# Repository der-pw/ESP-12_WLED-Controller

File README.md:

# ESP-12_WLED-Controller V1.3 

[English Version below](https://github.com/der-pw/ESP-12_WLED-Controller#english)

---

Designidee eines EPS-12(E/F) basierten NeoPixel (WS2812B, WS2811, SK6812)-Controller speziell für [WLED](https://github.com/Aircoookie/WLED) oder auch Alternativen.

### tl;dr
Ich habe einige Tests zur Stromaufnahme am ESP-32_WLED-Controller durchgeführt. Da beide Controller im Bereich des MOSFET gleich aufgebaut sind, lassen sich die Erkenntnisse übertragen.  
Let's talk about [maximum ratings](https://github.com/der-pw/ESP-32_WLED-Controller/blob/main/maximum_ratings.md)

### Übersicht:
 - [Versionen](https://github.com/der-pw/ESP-12_WLED-Controller#versionen)
 - [Gehäuse](https://github.com/der-pw/ESP-12_WLED-Controller#gehäuse) 
 - [Einstellungen](https://github.com/der-pw/ESP-12_WLED-Controller#einstellungen)
 - [Teileliste](https://github.com/der-pw/ESP-12_WLED-Controller#teileliste)
 - [Anschluss Hinweise](wiring.md) ->

Die Idee war es, einen Controller zu bauen, der mit Pegelwandler arbeitet um das Datensignal, welches der ESP8266 nur mit 3,3V Pegel ausgibt, auf die vom LED-Strip benötigten 5V zu setzen. Gerade bei langen Datenleitungen kann ein 3,3V-Pegel sich schneller "verwaschen". 
Als Levelshifter werwende ich einen **74LVC1G125**.
Zusätzlich kann die Versorgungsspannung für den LED-Strip über einen P-Kanal MOSFET abgeschaltet werden. Auch im ausgeschalteten Zustand verbrauchen die NEOPIXEL-Strips Strom (ca. 1mA/Pixel).   
Praktischerweise bietet WLED hier seit einiger Zeit, die Möglichkeit über einen frei definierten Pin ein "Relay" zu schalten.
Vor dem P-MOSFET sitzt ein weiterer N-MOSFET. Einmal funktioniert dieser als Treiber um den P-MOSFET mit 5V Logikpegel zu schalten und zum anderen als Inverter, damit der Haupt-MOSFET praktisch "active HIGH" am GPIO12 des ESP2866 durchschaltet.

### Versionen:
 - 0.9 erstes Layout veröffentlicht
 - 1.0 kleine Änderungen und Fehler beseitigt
 - - 1.01 C1 und C2 Korrektur der Werte (statt 10nF 10µF) hat keine Auswirkung auf die Platine
 - - 1.1 Gatewiderstand R9 hinzugefügt
 - - 1.2 Gatewiderstand Wert auf 300Ohm geändert
 - - 1.3 Platinenlayout überarbeitet  
 THT-MOSFET entfernt und dafür ...    
 Leiterbahn verbreitert und auf zwei Lagen verteilt  
 zweiter C2 Kondensator  
 Lötjumper unter R6 zum Überbrücken gesetzt  
 zweiter GND Anschluss am Terminal  
 Datenpin von IO4 auf IO2 gelegt [Fehler im Design](https://github.com/der-pw/ESP-12_WLED-Controller/issues/2#issuecomment-1024920433).

### Gehäuse

Es gibt ein simples Gehäuse. 
Die beiden Geäusehälften werden zusammen geklipst.
Die Platine wird mittels 2x5mm Linsenkopfschrauben (Grobgewinde) im Gehäuse befestigt.

### Einstellungen
Die Platine verwendet folgendes Pin-Setting.  
Auf **GPIO0** kann ein externer Button verwendet werden, zum Ein- und Ausschalten und zusätzlich initiert man darüber den Flashvorgang.  
An **GPIO2** hängt das Datensignal und über **GPIO12** wird der MOSFET geschaltet.

### Teileliste

| Refs | Qty | Component | Description |
| ----- | --- | ---- | ----------- |
| C1 | 1 | 10µF | 0805 10µF |
| C2 | 1 | 47F | 0805 47µF oder 22µF |
| aC2 | 1 | 100µF | alternativer Footprint in 1206 für größere Kerkos |
| C3, C5 | 2 | 100nF | 0805 100nF |
| C4 | 1 | 1000µF | Elko radial 1000µF 6.3V RM3.5 d=8mm l=11.5mm |
| D1 | 1 | Freilaufdiode | SS14 DO-214 |
| J1 | 1 | Screw_Terminal_01x05 |  |
| J2 | 1 | Conn_01x04_Male | Buchsenleiste RM2.54mm |
| JP1 | 1 | BTN/FLASH | Jumper mit Pinheader RM2.54 |
| JP2 | 1 | Jumper_2_Open | Lötbrücke auf der Rückseite für R6 |
| Q1 | 1 | IRLML6344 | MOSFET N-Kanal 30 V 5A SOT-23 |
| Q2 | 1 | IRF7410 | MOSFET P-Kanal -12 V -16A SO-8 |
| R1, R2, R3, R4, R5, R7, R8 | 7 | 10k | 0805 10kΩ |
| R6 | 1 | 470R | 0805 470Ω |
| R9 | 1 | 300R | 0805 300Ω |
| SW1 | 1 | SW_RST | 6mm x3.5mm Push Button SMD|
| U1 | 1 | TS1117-3.3 | Linearregler 3.3V fix alt. AMS1117-3.3, SOT-223 |
| U2 | 1 | ESP-12F | ESP-12F (ESP8266) Wifi-Modul |
| U4 | 1 | 74LVC1G125 | Single Buffer Gate Tri-State als Logic Level Converter, SOT-23-5 |

Diese Platine kann mit einem [fertigen Binary](https://install.wled.me/) verwendet werden.

## Dankeschön!  

Ein besonderer Dank geht an [Aircoookie](https://github.com/Aircoookie) und allen Beteiligten, die am [WLED](https://github.com/Aircoookie/WLED) Projekt mitarbeiten.

----
## English

### tl;dr
I did some power consumption tests on the ESP-32_WLED controller. Both controllers have the same structure in the MOSFET area, the results can be transferred.  
Let's talk about [maximum ratings](https://github.com/der-pw/ESP-32_WLED-Controller/blob/main/maximum_ratings.md)

----

Design idea of an EPS-12 (E / F) based NeoPixel (WS2812B, WS2811, SK6812) controller especially for WLED or alternatives.

Overview:
 - [Versions](https://github.com/der-pw/ESP-12_WLED-Controller#versions)
 - [Case](https://github.com/der-pw/ESP-12_WLED-Controller#case) 
 - [Settings](https://github.com/der-pw/ESP-12_WLED-Controller#settings)
 - [Parts list](https://github.com/der-pw/ESP-12_WLED-Controller#parts-list)
 - [Connecting Hints](wiring.md) ->

The idea was to build a controller that works with level converters to set the data signal, which the ESP8266 only outputs with a 3.3V level, to the 5V required by the LED strip. Especially with long data lines, a 3.3V level can "fading" more quickly.
As the level shifter I use a **74LVC1G125**.
In addition, the supply voltage for the LED strip can be switched off via a P-Channel MOSFET. Even when switched off, the NEOPIXEL strips consume electricity (approx. 1mA/pixel).
Conveniently, WLED offers the option of switching a "relay" via a freely defined pin. https://github.com/Aircoookie/WLED/issues/631#issuecomment-578551872
Another N-MOSFET sits in front of the P-MOSFET. On the one hand, this works as a driver to operate the P-MOSFET with a 5V logic level and on the other hand as an inverter, so that the main MOSFET switches through practically "active HIGH" on the GPIO12 of the ESP2866.

### Versions:
 - 0.9 first layout published
 - 1.0 minor changes and bugs fixed
 - - 1.01 C1 and C2 wrong Values fixed (10µF instead of 10nF) has no effects of the PCB
 - - 1.1 added gate resistor R9
 - - 1.2 change gate resisitr value to 300Ohm
 - - 1.3 board layout revised  
 THT MOSFET removed and for that...  
 Traces widened and divided onto two layers  
 second alternative C2 capacitor  
 Solder jumper placed under R6 for bridging  
 second GND connector on the terminal.  
 Data pin placed from IO4 to IO2 [Error in design](https://github.com/der-pw/ESP-12_WLED-Controller/issues/2#issuecomment-1024920433). 

### Case

There is a simple case. The two halves of the housing are clipped together. The circuit board is attached to the housing by means of 2x5mm pan head screws (coarse thread).

### Settings
The board uses the following pin setting.
An external button can be used on GPIO0 to switch it on and off and also to initiate the flash process.
The data signal is connected to GPIO2 and the MOSFET is switched via GPIO12.

### Parts list

| Refs | qty | components | Description |
| ----- | --- | ---- | ----------- |
| C1 | 1 | 10µF | 0805 10µF |
| C2 | 1 | 47F | 0805 47µF or 22µF |
| aC2 | 1 | 100µF | alternative footprint in 1206 for larger caps |
| C3, C5 | 2 | 100nF | 0805 100nF |
| C4 | 1 | 1000µF | Capacitor radial 1000µF 6.3V pich3.5 d=8mm l=11.5mm |
| D1 | 1 | Flyback diode | SS14 DO-214 |
| J1 | 1 | Screw_Terminal_01x05 | |
| J2 | 1 | Conn_01x04_Male | Socket strip pitch 2.54mm |
| JP1 | 1 | BTN/FLASH | Jumper with pin header pitch 2.54 |
| JP2 | 1 | Jumper_2_Open | Solder bridge on the back for R6 |
| Q1 | 1 | IRLML6344 | MOSFET N-channel 30V 5A SOT-23 |
| Q2 | 1 | IRF7410 | MOSFET P-channel -12V -16A SO-8 |
| R1, R2, R3, R4, R5, R7, R8 | 7 | 10k | 0805 10kΩ |
| R6 | 1 | 470R | 0805 470Ω |
| R9 | 1 | 300R | 0805 300Ω |
| SW1 | 1 | SW_RST | 6mm x3.5mm Push Button SMD|
| U1 | 1 | TS1117-3.3 | Linear regulator 3.3V fix old. AMS1117-3.3, SOT-223 |
| U2 | 1 | ESP-12F | ESP-12F (ESP8266) Wifi Module |
| U4 | 1 | 74LVC1G125 | Single Buffer Gate Tri-State as Logic Level Converter, SOT-23-5 |

PCB can be used with a [pre compiled binary](https://install.wled.me/).

## Thanks!  

Special thanks to [Aircoookie](https://github.com/Aircoookie) and all the contributors at the [WLED](https://github.com/Aircoookie/WLED) project.

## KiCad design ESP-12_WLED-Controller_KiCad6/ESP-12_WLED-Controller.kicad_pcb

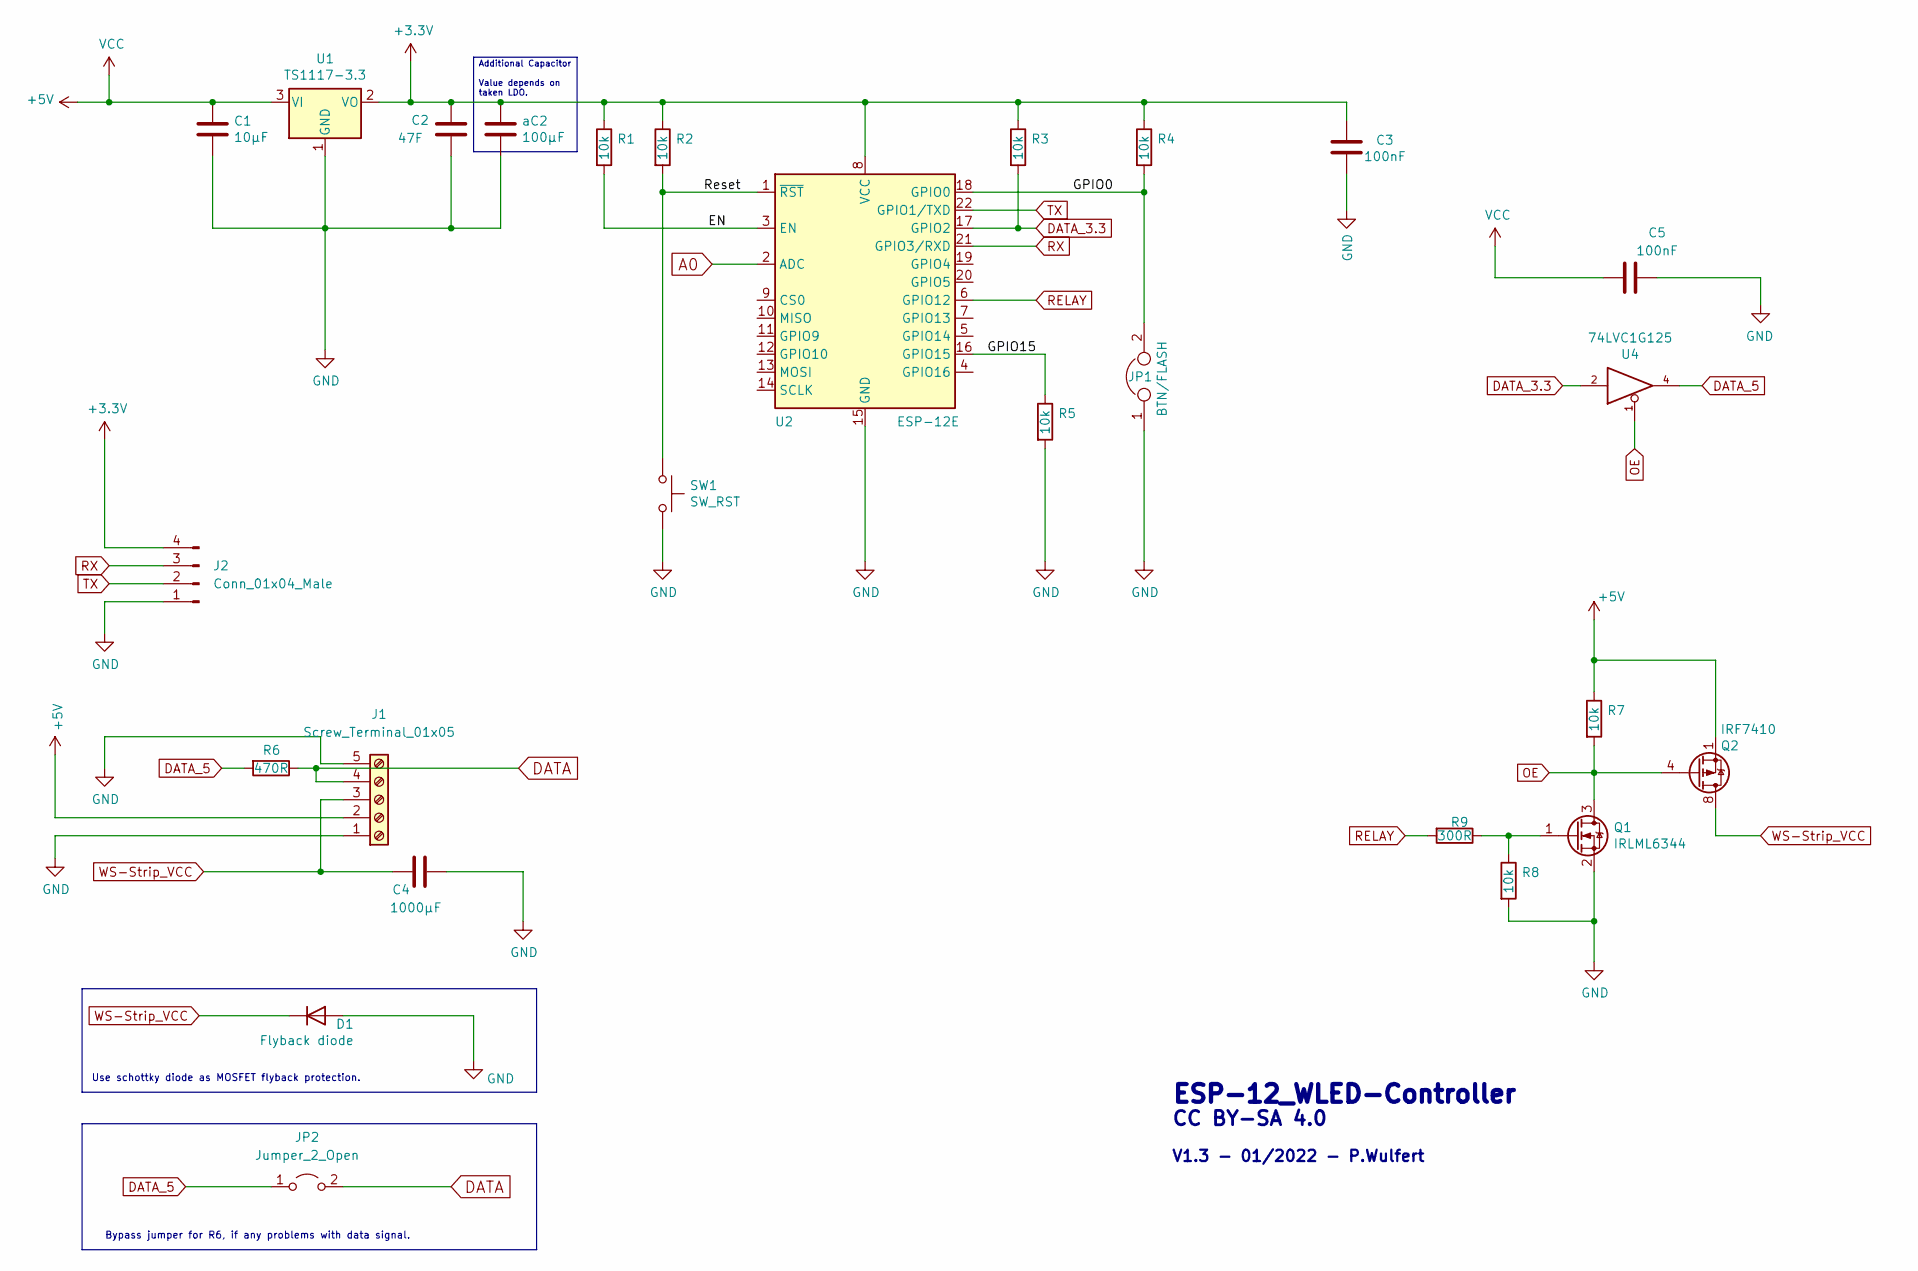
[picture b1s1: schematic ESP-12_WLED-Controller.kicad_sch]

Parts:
C1: 10µF; C_0805_2012Metric_Pad1.18x1.45mm_HandSolder; LCSC C1713
C2: 47F; C_0805_2012Metric_Pad1.18x1.45mm_HandSolder; LCSC C1713
C3, C5: 100nF; C_0805_2012Metric_Pad1.18x1.45mm_HandSolder; LCSC C49678
C4: 1000µF; CP_Radial_D8.0mm_P3.50mm; LCSC C189254
D1: Flyback diode; D_SMA_Handsoldering; LCSC C2480
J1: Screw_Terminal_01x05; TerminalBlock_bornier-5_P5.08mm
J2: Conn_01x04_Male; PinSocket_1x04_P2.54mm_Vertical
JP1: BTN/FLASH; PinHeader_1x02_P2.54mm_Vertical; LCSC C390678
JP2: Jumper_2_Open; SolderJumper-2_P1.3mm_Open_RoundedPad1.0x1.5mm
Q1: IRLML6344; SOT-23; LCSC C693370
Q2: IRF7410; SOIC-8_3.9x4.9mm_P1.27mm; LCSC C152423
R1, R2, R3, R4, R5, R7, R8: 10k; R_0805_2012Metric_Pad1.20x1.40mm_HandSolder; LCSC C17617
R6: 470R; R_0805_2012Metric_Pad1.20x1.40mm_HandSolder; LCSC C114564
R9: 300R; R_0805_2012Metric_Pad1.20x1.40mm_HandSolder; LCSC C17617
SW1: SW_RST; SW_SPST_CK_RS282G05A3
U1: TS1117-3.3; SOT-223-3_TabPin2; LCSC C410833
U2: ESP-12E; LCSC C82891
U4: 74LVC1G125; SOT-23-5; LCSC C12518
aC2: 100µF; C_1206_3216Metric_Pad1.33x1.80mm_HandSolder

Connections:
+3V3: C2.1, C3.2, J2.4, R1.1, R2.1, R3.1, R4.1, U1.2 (VO), U2.8 (VCC), aC2.1
+5V: C1.1, C5.2, J1.2, Q2.1 (S), Q2.2 (S), Q2.3 (S), R7.1, U1.3 (VI), U4.5 (VCC)
/EN: R1.2, U2.3 (EN)
/GPIO0: JP1.2, R4.2, U2.18 (GPIO0)
/GPIO15: R5.1, U2.16 (GPIO15)
/Reset: R2.2, SW1.1, U2.1 (~RST)
A0: U2.2 (ADC)
DATA: J1.4, JP2.2 (B), R6.1
DATA_3.3: R3.2, U2.17 (GPIO2), U4.2
DATA_5: JP2.1 (A), R6.2, U4.4
GND: C1.2, C2.2, C3.1, C4.2, C5.1, D1.2 (A), J1.1, J1.5, J2.1, JP1.1, Q1.2 (S), R5.2, R8.2, SW1.2, U1.1 (GND), U2.15 (GND), U4.3 (GND), aC2.2
unnamed: Q1.1 (G), R8.1, R9.1
OE: Q1.3 (D), Q2.4 (G), R7.2, U4.1
RELAY: R9.2, U2.6 (GPIO12)
RX: J2.3, U2.21 (GPIO3/RXD)
TX: J2.2, U2.22 (GPIO1/TXD)
WS-Strip_VCC: C4.1, D1.1 (K), J1.3, Q2.5 (D), Q2.6 (D), Q2.7 (D), Q2.8 (D)

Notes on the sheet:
ESP-12_WLED-Controller
Bypass jumper for R6, if any problems with data signal.
Additional Capacitor Value depends on taken LDO.
V1.3 - 01/2022 - P.Wulfert
CC BY-SA 4.0
Use schottky diode as MOSFET flyback protection.

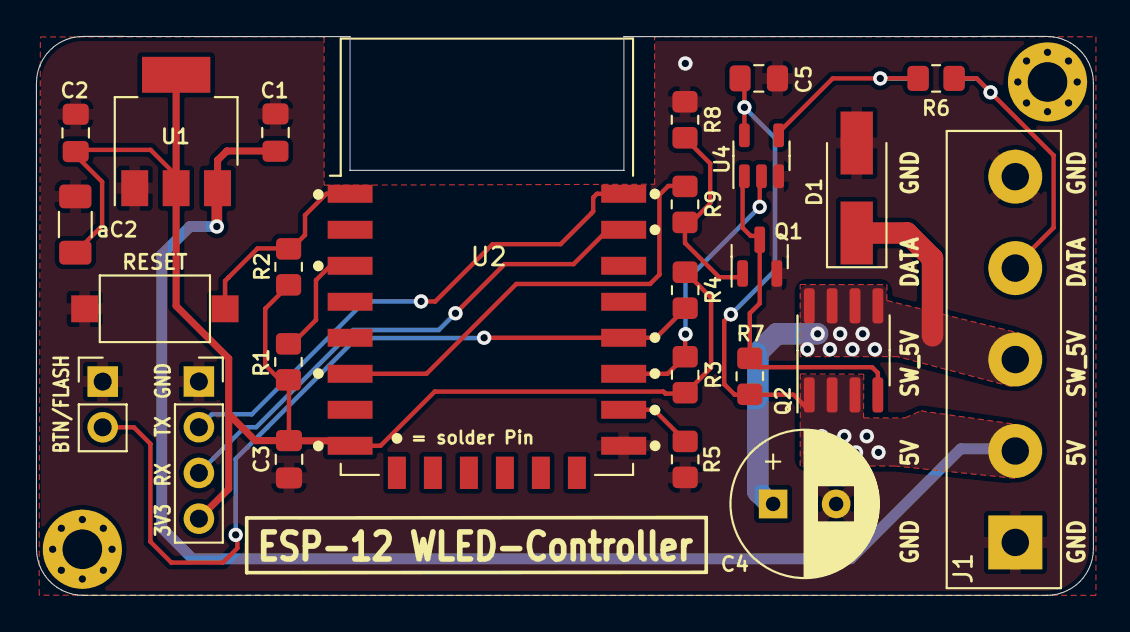
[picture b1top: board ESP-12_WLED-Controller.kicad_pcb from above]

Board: 2 copper layers, 58.7 x 31.0 mm, 26 parts (1 on the bottom side), 16 nets.

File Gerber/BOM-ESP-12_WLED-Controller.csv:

Comment,Designator,Footprint,LCSC
470R,R6,R_0805_2012Metric_Pad1.20x1.40mm_HandSolder,C114564
74LVC1G125,U4,SOT-23-5,C12518
IRF7410,Q2,SOIC-8_3.9x4.9mm_P1.27mm,C152423
47F,C2,C_0805_2012Metric_Pad1.18x1.45mm_HandSolder,C16780
10µF,C1,C_0805_2012Metric_Pad1.18x1.45mm_HandSolder,C1713
10k,"R1,R2,R3,R4,R5,R7,R8",R_0805_2012Metric_Pad1.20x1.40mm_HandSolder,C17414
300R,R9,R_0805_2012Metric_Pad1.20x1.40mm_HandSolder,C17617
1000µF,C4,CP_Radial_D8.0mm_P3.50mm,C189254
Flyback diode,D1,D_SMA_Handsoldering,C2480
SW_RST,SW1,SW_SPST_CK_RS282G05A3,C319331
BTN/FLASH,JP1,PinHeader_1x02_P2.54mm_Vertical,C390678
100nF,"C3,C5",C_0805_2012Metric_Pad1.18x1.45mm_HandSolder,C49678
TS1117-3.3,U1,SOT-223-3_TabPin2,C6186
IRLML6344,Q1,SOT-23,C693370
ESP-12E,U2,ESP-12E,C82891
Screw_Terminal_01x05,J1,TerminalBlock_bornier-5_P5.08mm,
100µF,aC2,C_1206_3216Metric_Pad1.33x1.80mm_HandSolder,
Conn_01x04_Male,J2,PinSocket_1x04_P2.54mm_Vertical,
Jumper_2_Open,JP2,SolderJumper-2_P1.3mm_Open_RoundedPad1.0x1.5mm,

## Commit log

2021-06-18 upload
2021-06-21 add IRF7410 Power MOSFET
2021-06-22 LLC changes
2021-06-23 some changes
    single Terminal-Block
    parts clean up
    edit footprints for handsolder
2021-06-23 initial Start
    ... now it's online
2021-06-24 some PCB updates
2021-07-03 Update to V1.0
    clean schematic
    add description
    TX <-> RX
2021-07-03 add simple Case
2021-07-03 Update README.md
    added more text
2021-07-03 update schematic
2021-07-06 Update README.md
    add Parts list thanks to stan23
2021-07-13 Update README.md
    add english version
2021-11-07 V 1.01
    fixed the Values at C1 and C2
2021-11-07 V 1.01
    update schematic to 1.01
2021-12-12 Upgrade to V1.1
    Added R9 gate resistor to PCB
2021-12-14 Update README.md
    sort part list
2021-12-22 Update ESP-12_WLED-Controller.pdf
    fix description
2021-12-26 update documentation
2021-12-26 typo
2021-12-26 small typo
2021-12-26 Update wiring.md
    add some informations
2021-12-27 additions to the documentation
2021-12-28 aditional updates
2022-01-06 Upgrade to KiCad6
2022-01-12 V1.2
    change Gate Resistor to 300 Ohm
2022-01-12 Update README.md
    add V1.2
2022-02-01 Update README.md
    complete parts list
2022-02-04 update
    - Pinsetting
    - Case bottom
    - Gerbers
2022-02-05 Update PCB-top.jpg
    replace rendering
2022-02-06 update BOM

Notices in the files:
README.md:
License: CC BY-SA 4.0
